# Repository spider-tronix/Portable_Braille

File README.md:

# Portable Braille

## Abstract:
Braille is a system of raised dots that allows visually impaired people to read tactilely. Currently, the number of books written in Braille script is less and the cost is high. This project is an approach to solve the problem of unavailability of many of the books and texts in Braille script. The Portable Braille consists of a camera module which captures the image of a printed text material and converts it into text format by using Optical Character Recognition(OCR). The characters in the text are converted into Braille characters(3x2 matrix form) and fed to the actuators. The actuators are the pins in the head of a dot matrix printer. The pins are actuated in such a way that it creates pressure at required points in the fingertip similar to how pressure felt when placed on an embossed braille character. By this way the device sends character by character to the user’s fingertip through the actuators.
These characters will be sent with appropriate delays to make the user understand words/sentences. Hence a given printed text material can be understood by the blind person through his/her sense of touch.

## Team:

  • [Aditya Kumar Singh](https://github.com/adityasingh3007)

  • [Raj Kumar Bhagat](https://github.com/Rajk0520)

  • [Ruphan S](https://github.com/ruphan)

  • [Yash Patel](https://github.com/yash270200)

## Working Video Demonstration:

# Repository Organized.

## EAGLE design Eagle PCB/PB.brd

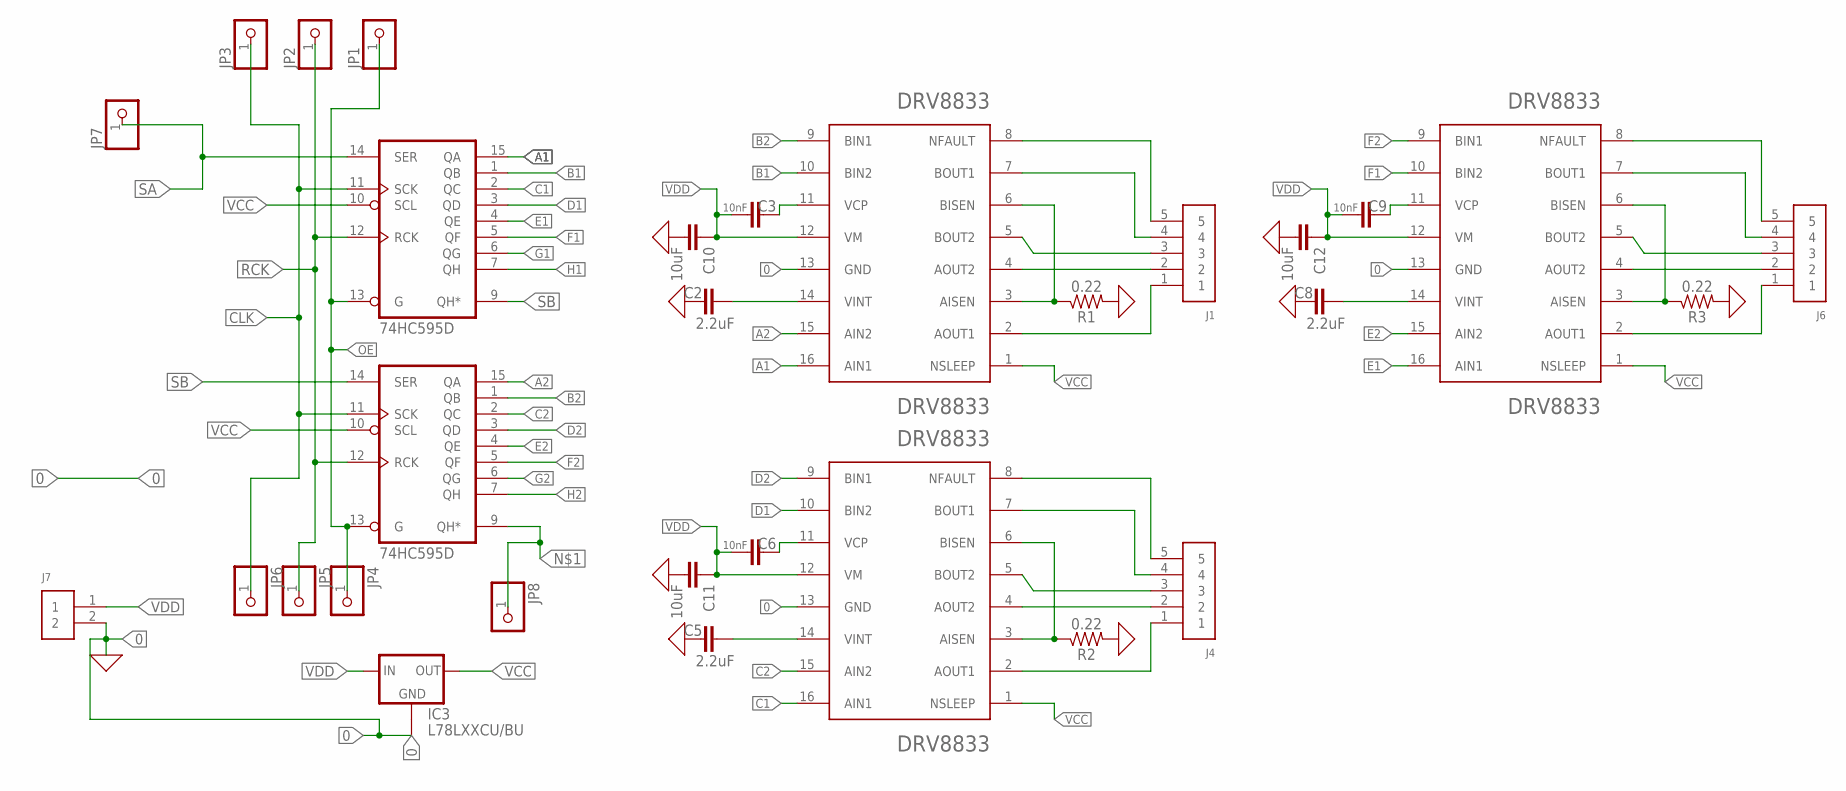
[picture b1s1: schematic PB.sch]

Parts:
C2, C5, C8: 2.2uF; 0603
C3, C6, C9: 10nF; 0603
C10, C11, C12: 10uF; 0805
DRV8833PWP1, DRV8833PWP2, DRV8833PWP3: DRV8833; SOP65P640X120-17N
IC1, IC2: 74HC595D; SO16
IC3: L78LXXCU/BU; SOT89
J1, J4, J6: 61300511121
J7: 61300211121
JP1, JP2, JP3, JP4, JP5, JP6, JP7, JP8: PINHD-1X1; 1X01
R1, R2, R3: 0.22; 0805

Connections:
0: C2.2, C5.2, C8.2, C10.2, C11.2, C12.2, DRV8833PWP1.13 (GND), DRV8833PWP2.13 (GND), DRV8833PWP3.13 (GND), IC1.8 (GND), IC2.8 (GND), IC3.4 (GND1), J7.2, R1.2, R2.2, R3.2
A1: DRV8833PWP1.16 (AIN1), IC1.15 (QA)
A2: DRV8833PWP1.15 (AIN2), IC2.15 (QA)
B1: DRV8833PWP1.10 (BIN2), IC1.1 (QB)
B2: DRV8833PWP1.9 (BIN1), IC2.1 (QB)
C1: DRV8833PWP2.16 (AIN1), IC1.2 (QC)
C2: DRV8833PWP2.15 (AIN2), IC2.2 (QC)
CLK: IC1.11 (SCK), IC2.11 (SCK), JP3.1, JP6.1
D1: DRV8833PWP2.10 (BIN2), IC1.3 (QD)
D2: DRV8833PWP2.9 (BIN1), IC2.3 (QD)
E1: DRV8833PWP3.16 (AIN1), IC1.4 (QE)
E2: DRV8833PWP3.15 (AIN2), IC2.4 (QE)
F1: DRV8833PWP3.10 (BIN2), IC1.5 (QF)
F2: DRV8833PWP3.9 (BIN1), IC2.5 (QF)
G1: IC1.6 (QG)
G2: IC2.6 (QG)
H1: IC1.7 (QH)
H2: IC2.7 (QH)
unnamed: IC2.9 (QH*), JP8.1
unnamed: C2.1, DRV8833PWP1.14 (VINT)
unnamed: C3.1, DRV8833PWP1.11 (VCP)
unnamed: DRV8833PWP1.3 (AISEN), DRV8833PWP1.6 (BISEN), R1.1
unnamed: DRV8833PWP1.8 (NFAULT), J1.5
unnamed: DRV8833PWP1.7 (BOUT1), J1.4
unnamed: DRV8833PWP1.2 (AOUT1), J1.1
unnamed: DRV8833PWP1.4 (AOUT2), J1.2
unnamed: DRV8833PWP1.5 (BOUT2), J1.3
unnamed: C5.1, DRV8833PWP2.14 (VINT)
unnamed: C6.1, DRV8833PWP2.11 (VCP)
unnamed: DRV8833PWP2.3 (AISEN), DRV8833PWP2.6 (BISEN), R2.1
unnamed: DRV8833PWP2.8 (NFAULT), J4.5
unnamed: DRV8833PWP2.7 (BOUT1), J4.4
unnamed: DRV8833PWP2.2 (AOUT1), J4.1
unnamed: DRV8833PWP2.4 (AOUT2), J4.2
unnamed: DRV8833PWP2.5 (BOUT2), J4.3
unnamed: C8.1, DRV8833PWP3.14 (VINT)
unnamed: C9.1, DRV8833PWP3.11 (VCP)
unnamed: DRV8833PWP3.3 (AISEN), DRV8833PWP3.6 (BISEN), R3.1
unnamed: DRV8833PWP3.8 (NFAULT), J6.5
unnamed: DRV8833PWP3.7 (BOUT1), J6.4
unnamed: DRV8833PWP3.2 (AOUT1), J6.1
unnamed: DRV8833PWP3.4 (AOUT2), J6.2
unnamed: DRV8833PWP3.5 (BOUT2), J6.3
OE: IC1.13 (G), IC2.13 (G), JP1.1, JP4.1
RCK: IC1.12 (RCK), IC2.12 (RCK), JP2.1, JP5.1
SA: IC1.14 (SER), JP7.1
SB: IC1.9 (QH*), IC2.14 (SER)
VCC: DRV8833PWP1.1 (NSLEEP), DRV8833PWP2.1 (NSLEEP), DRV8833PWP3.1 (NSLEEP), IC1.10 (SCL), IC1.16 (VCC), IC2.10 (SCL), IC2.16 (VCC), IC3.1 (OUT)
VDD: C3.2, C6.2, C9.2, C10.1, C11.1, C12.1, DRV8833PWP1.12 (VM), DRV8833PWP2.12 (VM), DRV8833PWP3.12 (VM), IC3.3 (IN), J7.1

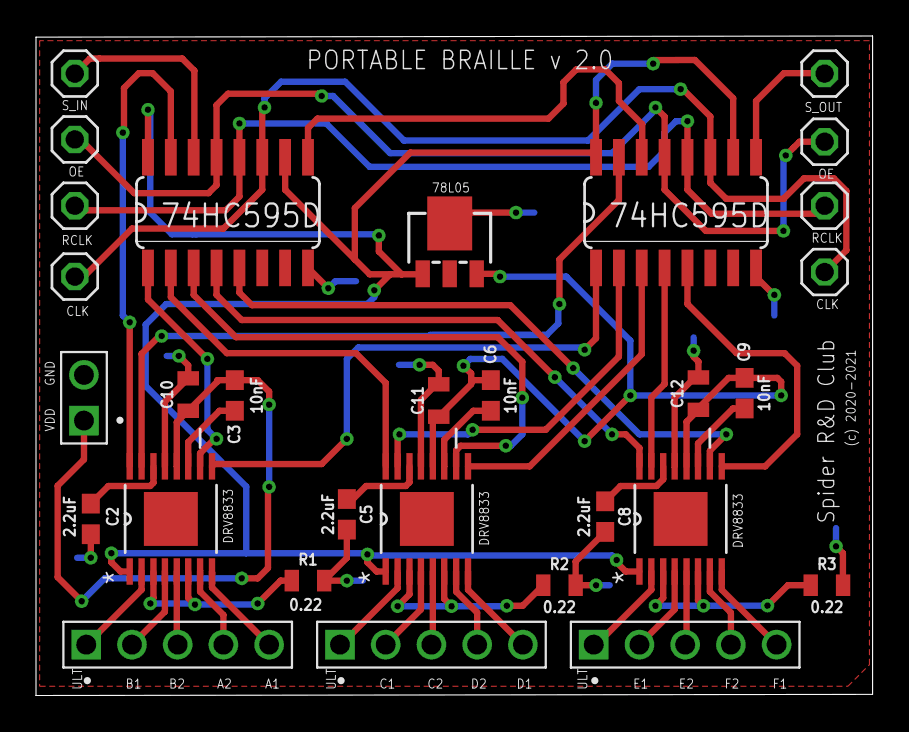
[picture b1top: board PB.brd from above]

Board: 2 copper layers, 46.5 x 36.6 mm, 30 parts (0 on the bottom side), 45 nets.

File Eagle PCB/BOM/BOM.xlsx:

Qty | Designator | Footprint | LCSC Part # | Description
3 | DRV8833PWP1, DRV8833PWP2, DRV8833PWP3 | SOP65P640X120-17N | C50506
8 | JP1, JP2, JP3, JP4, JP5, JP6, JP7, JP8 | 1X01 |  | PIN HEADER
3 | R1, R2, R3 | 0805 | C25336 | 0.22Ω resistor
3 | C3, C6, C9 | 0603 | C7248 | 0.01uF/10nF/10,000pF ceramic capacitors
3 | C1, C4, C10 | 0805 | C307523 | 10.0µF ceramic capacitors
3 | C2, C5, C8 | 0603 | C23630 | 2.2µF ceramic capacitors
1 | J7 | 61300211121 |  | CONN HEADER VERT 2POS 2.54MM
3 | J1, J4, J6 | 61300511121 |  | CONN HEADER VERT 5POS 2.54MM
2 | IC1, IC2 | SO16 | C431479 | 8-bit SHIFT REGISTER, output latch
1 | IC3 | SOT89 | C83866 | VOLTAGE REGULATOR

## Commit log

2019-06-02 Repository initiated.
2019-06-15 License added
2019-08-15 Actuator, Tesseract_Tester file documented
2019-08-29 Initiating v2.0
2019-09-01 Modification needed in actuator added
2019-09-02 Grade 2 minor bug fixed
2019-09-05 Grade 1 Braille optimized
2019-09-11 Basic solenoid schematic to reduce power consumption
2019-09-12 Optimised for Solenoid JY0415
2019-10-01 post preprocessing for ocr text
2019-10-01 .gitignore added
2019-10-01 fixed image problem
2019-10-12 post process techniques and test images
2019-10-15 SSH file transfer script added
2019-10-15 SSH Image file transfer script added
2019-10-15 delete
2019-10-15 Access Point creation script added
2019-12-22 Camera Calibration Matrix
2019-12-22 Basic 3D Design of the setup
2019-12-23 Added extentsion mechanism for placing the book
2019-12-23 Added Camera Setup
2019-12-23 Added Camera Mechanism
2020-01-19 Revert "Added Camera Mechanism"
    This reverts commit 3f9a1a776d8217dc012b96e9d371ecbb299fbd20.
2020-01-19 Added solenoid CAD models
2020-01-19 Added Single Braille Cell
2020-01-20 Bluetooth comm. code added
2020-01-20 PCB schematic and board added
2020-01-21 Added complete actuator setup
2020-01-21 Text segmenter for BT comm. code added
2020-01-22 page transformation function
2020-01-23 Two way Bluetooth comm. and Segmenter code added
2020-01-25 Control Unit code, for shutdwon and MOTD added
2020-01-26 client socket for table detection
2020-01-27 Final PCB schematic and board added.
2020-02-03 BT serial communication file added
2020-02-03 SIPO code added
2020-02-05 PCB updated with common serial input.
2020-02-05 Gerber files and BOM file added
2020-02-18 SIPO interfacing Lib created and added
2020-02-18 Final Nano module added
2020-02-20 Hand tracking based SIPO content alteration part added

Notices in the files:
Eagle PCB/PB.brd:
(c) 2020-2021
parts and their libraries:
SparkFun-Capacitors: Licensing: Creative Commons ShareAlike 4.0 International - https://creativecommons.org/licenses/by-sa/4.0
